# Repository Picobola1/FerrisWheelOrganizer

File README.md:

# A Ferris Wheel That Organizes
P.S This is a project that you randomly think would be funny but end actully makeing it.

This project is a ferris wheel that you can put screws and other small items in, so when you push a button, it rotates the wheel one seat(holder thingy) so you can grab whatever you need then go to the next seat.

I made this project beause i though it would be funny and a cool desktoy

the hardest part was defenitly modeleing beacuse i am pretty new to onshape and i have never built somehting so big with it before. 

I learned that i really enjoy listing to music while working on it and that i should plan and save files a lot more.

# To build it

24x M3x12 screws (i get mine from this kit [Here](https://www.amazon.com/HanTof-Phillips-Assortment-Eletronic-Stainless/dp/B0C4T1ZDYL) i also use this screw kit for other projects tpp :) )

1x 28BYJ-48 DC Stepper Motor 

1x ULN2003 Driver Test Module Board (you can get both [Here](https://www.amazon.com/Aoicrie-28BYJ-48-Stepper-ULN2003-Arduino/dp/B07Z4BCY34/ref=sr_1_18?crid=30050OUVGY3IK&dib=eyJ2IjoiMSJ9.4H5mpY-xIVvTQ6Eu0ElQQyx78D2V2-c2F2viQ88cHiyxLSFPU7p_H6jLMM5rM2Pp9f4mAYkoUhALU2quD43HG_aMONg68MmZ2DaTBeR3hcnlQBhZBcOzhS3Y3RNNsGsDzrrSdXtXVqw4l3c2jbkXNIHOEM2RvwsW0aHa2bCH63sEDpWlfRnqr4-50PPtt0l0thLjaa-dxNKJ7Ksv6xj-bLVRP6vb6Vl8F-y-Su2ypJs.hxkWC0xT_ZFts2pBB3f8EnZUKG_TjAzSC9bmYVCKEYs&dib_tag=se&keywords=unipolar+stepper+motor&qid=1753672978&sprefix=stepper+motor+uni%2Caps%2C176&sr=8-18))

3x 6mm through-hole momentary push buttons, 4.3mm height ([Link](https://www.amazon.com/Momentary-Tactile-Through-Breadboard-Friendly/dp/B07WF76VHT/ref=sxin_16_pa_sp_search_thematic_sspa?content-id=amzn1.sym.3afbfb03-37f9-433d-812b-5618f5fce9ff%3Aamzn1.sym.3afbfb03-37f9-433d-812b-5618f5fce9ff&cv_ct_cx=push+button+amazon&hvadid=695372375513&hvdev=c&hvexpln=67&hvlocphy=9051519&hvnetw=g&hvocijid=13079691696891314430--&hvqmt=e&hvrand=13079691696891314430&hvtargid=kwd-901175987013&hydadcr=7496_13184019&keywords=push+button+amazon&mcid=ce58c0ce72cf3e5182a4e7b389dc283b&pd_rd_i=B07WF76VHT&pd_rd_r=e070f955-469c-4ea4-88f3-a911c28ee738&pd_rd_w=jgkFu&pd_rd_wg=xhqKh&pf_rd_p=3afbfb03-37f9-433d-812b-5618f5fce9ff&pf_rd_r=PA9J6DZHGZFRM29VR1PD&qid=1754704883&sbo=RZvfv%2F%2FHxDF%2BO5021pAnSA%3D%3D&sr=1-2-6024b2a3-78e4-4fed-8fed-e1613be3bcce-spons&sp_csd=d2lkZ2V0TmFtZT1zcF9zZWFyY2hfdGhlbWF0aWM&psc=1))

1x Arduino Nano ([Here](https://www.amazon.com/EASTPONDO-Microcontroller-Pre-soldered-Compatible-Arduino/dp/B0DFQ437TH/ref=sr_1_7_sspa?dib=eyJ2IjoiMSJ9.gA_RBHQKlL9fqee7OwDWK3TVa4f1jG2BDdr1cCnXe_MdE0s8wO5aJ8pkLaNAC-VVU5JtYG8JwmCtjiEy8soICr3GixwP0JBQigJ8H5mRijb5HocePXsI_XiaRH_7kLuhgRHpgfcrok9yoqa0V87dT0czxmASb9eGAirYZVxiweozVjGFWz7rgMowS-gMH8vKLY7pfJAK1bS5o5yrIKoTh1h56r2aUwyqqAmVj4dNNIE.HUR7PR1dLxfPpBB7sd6zurFShn8jE-4tTOO5A919Ofk&dib_tag=se&hvadid=695375672094&hvdev=c&hvexpln=67&hvlocphy=9051519&hvnetw=g&hvocijid=13633693633943766230--&hvqmt=e&hvrand=13633693633943766230&hvtargid=kwd-362855578768&hydadcr=18009_13447378&keywords=amazon+arduino+nano&mcid=ac8313c9e7bd3a1ebb1392b633aeedd3&qid=1754705207&refinements=p_36%3A-1700&rnid=386442011&sr=8-7-spons&sp_csd=d2lkZ2V0TmFtZT1zcF9tdGY&psc=1))

1x Pin Header 1x5 (for pcb)

1x Pin Header 1x2 (for pcb)

breadboard and wires for testing the hardware before using the grb to manufacutre the pcb.

All of the parts 3d printed or someother way like resin (20% percent infill is fine but it doesnt really matter)
1x of everything execpt for 3x buttons and however many cargo/ holder you want (max is 8)

# Instructions

Once you have all of the parts, go ahead and use this schematic to help you wire it with a breadboard or if your brave just order the pcb

# Step 1

lay the base on its side and put the main wheel through the hole on the base with the middle part holding the 2 wheels together then slide in the cargo/holder that you want and screw them in with the M3 12mm screws.

# Step 2 

put the second base on top of step 1 so it aligns with the screw holes and screw it in with the M3 12mm screws.

# Step 3 

You have now finsihed the Ferris Wheel now time for the controller. Note this does have to be close to the ferris wheel unless your stepper motor has really long wires.

First insert the pcb into the box and wire the stuff from the pcb up (At the bottem) then hot glue or glue the 3 buttons onto the buttons and put the top on, use M3 12mm screws.

# Step 4 

Now just upload the code and plugin the power :) have fun.

# PCB guide 

to plug every thing in the 2 pins are for power and gnd , the 5 pins are for the motor driver 4 input pins, and glue the buttons onto the push buttons and you are all set

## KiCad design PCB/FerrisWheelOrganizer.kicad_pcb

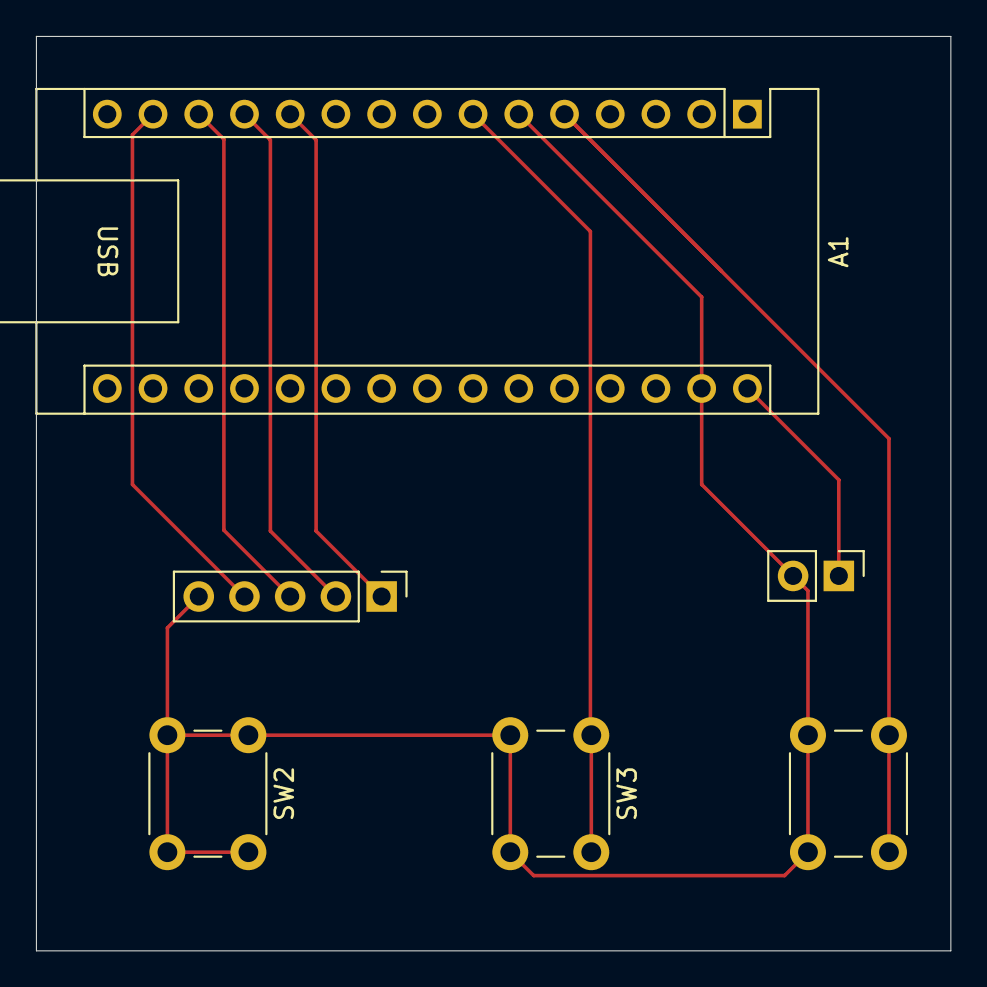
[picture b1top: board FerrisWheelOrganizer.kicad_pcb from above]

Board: 2 copper layers, 50.8 x 50.8 mm, 6 parts (0 on the bottom side), 8 nets.

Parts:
A1: Arduino_Nano_v3.x; Arduino_Nano
BT1: Battery; PinHeader_1x02_P2.54mm_Vertical
J1: Conn_01x05_Socket; PinHeader_1x05_P2.54mm_Vertical
SW1, SW2, SW3: SW_Push; SW_PUSH_6mm_H4.3mm

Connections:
unnamed: A1.5 (D2), SW1.1
unnamed: A1.6 (D3), A1.29 (GND), BT1.2 (-), J1.5, SW1.2, SW2.1, SW2.2, SW3.2
unnamed: A1.7 (D4), SW3.1
unnamed: A1.11 (D8), J1.1
unnamed: A1.12 (D9), J1.2
unnamed: A1.13 (D10), J1.3
unnamed: A1.14 (D11), J1.4
unnamed: A1.30 (VIN), BT1.1 (+)
